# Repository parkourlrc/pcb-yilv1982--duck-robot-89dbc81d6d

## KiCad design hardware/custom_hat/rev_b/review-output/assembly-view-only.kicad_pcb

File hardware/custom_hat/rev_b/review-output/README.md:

# Rev B.0审查输出：禁止下单或制造

此处是同源审查件，成本和制造准入尚未验收，**不是可付款/可制造交付包**。`manifest.json`记录源哈希、69个拟装件、30个归并组和检查状态。

- `gerbers/`为两层RS-274X、钻孔及当前制造层，用于DFM复查。未完成最终工厂接单和封装/丝印核准，不上传旧Y6/Y7/Y8替换文件。
- `bom-grouped.csv`按精确MPN/C编号/封装/厂商归并，功能单独列；数量为每板数量，下单数量仍5片。30组中尚有精确货号/厂商规范待复核，不代表锁料。
- `cpl-all-fitted.csv`包括63个SMT和6个THT的全部69位号；THT含底面J101母座，需工厂在SMT后插装焊接。不能把同一面SMT坐标等同于经济型接单批准。
- `schematic.pdf`为主图加8个功能页；`erc.json`、`drc.json`为原生检查报告。
- 数量、备损、最低上机数、焊接工序、税费和价格必须由新B版完整报价确认。无付款授权；自由文本备注留空。

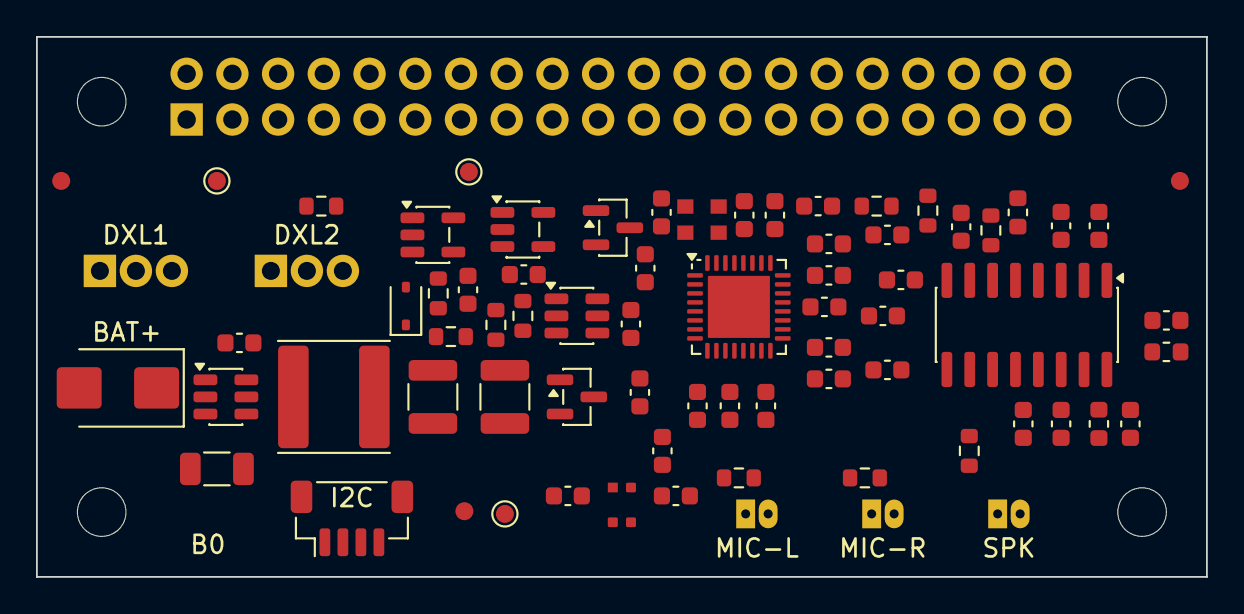
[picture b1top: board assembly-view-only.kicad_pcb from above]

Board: 2 copper layers, 65.0 x 30.0 mm, 79 parts (1 on the bottom side), 41 nets, no tracks yet.

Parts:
C301: C_1206_3216Metric
C302, C305, C401, C402, C701, C702, C703, C704, C705, C706, C707, C708, C709, C710, C711, C712, C713, C721, C722, C723, C724, C725, C731, C732, C733, C734, C735, C736, C737, C738, C739, C740: C_0603_1608Metric
C303, C304: C_1210_3225Metric
D301: D_SMB
D401: D_SOD-323
FB701, FB702, FB703: L_0603_1608Metric
FID1, FID2, FID3: Fiducial_1mm_Mask2mm_B
H1, H2: MountingHole_2.7_M2.5_Head4.5
H3, H4: MountingHole_2.7mm_M2.5
J101: Radxa40P_Zhouri_B
J401, J402: AMP2007_3P_B
J502: JST_SH_BM04B-SRSS-TB_1x04-1MP_P1.00mm_Vertical
J505, J506, J507: A1251_2P_B
L301: L_Sunlord_SWPA6045S
MK701: LMA2718_B
Q301: SOT-23
R301, R401, R402, R403, R404, R501, R502, R701, R721, R722, R731: R_0603_1608Metric
TP801, TP802, TP803: TestPoint_Pad_D1.0mm
U301, U302: TSOT-23-6
U701: TI_RHB0032E_AIC3104_EP345
U702: UMW_XC6206_SOT23_B
U801, U802: SOT-23-5
U803: SOIC-16_3.9x9.9mm_P1.27mm
Y701: YXC_2520_YSO110TR_B

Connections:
+1V8_CODEC: C703.1, C704.1, U701.32, U702.3
+3V3: C401.1, C402.1, C702.1, C705.1, C706.1, C707.1, C708.1, C709.1, C710.1, C711.1, C712.1, C713.1, C721.1, J101.1, J101.17, J502.2, MK701.4, R402.2, R403.2, R501.1, R502.1, R701.1, R731.1, TP803.1, U701.7, U701.18, U701.24, U701.25, U702.2, U801.5, U802.5, U803.5, U803.9, Y701.1, Y701.4
+5V: C734.1, C735.1, C736.1, C737.1, FB701.1, J101.2, J101.4, Q301.3, TP802.1, U302.6, U803.4, U803.13
+5V_PRE_IDEAL: C303.1, C304.1, L301.2, Q301.2, U301.1, U302.4
AMP_LEFT_INPUT: C731.2, U803.7
AMP_RIGHT_INPUT: C732.2, U803.10
AMP_R_N_RAW: FB702.1, U803.14
AMP_R_P_RAW: FB703.1, U803.16
AMP_VDD_FILT: C738.1, FB701.2, U803.6
AMP_VREF: C733.1, U803.8
AUDIO_AMP_EN: R731.2, U803.12
AUDIO_MCLK: U701.1, Y701.3
BUCK_BST: C302.1, U301.6
BUCK_SW: C302.2, L301.1, U301.5
CODEC_LEFT_LOP: C731.1, U701.27
CODEC_RIGHT_LOP: C732.1, U701.29
CODEC_RST: C701.1, J101.33, R701.2, U701.31
DXL_DATA: D401.1, J401.3, J402.3, R404.2
DXL_DATA_INT: R403.1, R404.1, U801.4, U802.2
DXL_DIR: J101.11, R401.1, U801.1, U802.1
I2C5_SCL: J101.29, J502.4, R502.2, U701.8
I2C5_SDA: J101.31, J502.3, R501.2, U701.9
I2S_BCLK: J101.12, U701.2
I2S_LRCK: J101.35, U701.3
I2S_SDI: J101.38, U701.5
I2S_SDO: J101.40, U701.4
IDEAL_GATE: Q301.1, U302.5
IDEAL_VS: C305.1, R301.2, U302.1
MICBIAS: C725.1, R721.1, R722.1, U701.15
MIC_EXT_L: C723.1, J505.2, R721.2
MIC_EXT_L_AC: C723.2, U701.10
MIC_EXT_R: C724.1, J507.2, R722.2
MIC_EXT_R_AC: C724.2, U701.12
MIC_ONBOARD_AC: C722.2, U701.16
MIC_ONBOARD_OUT: C722.1, MK701.1
POWER_GND: C301.2, C303.2, C304.2, C305.2, C401.2, C402.2, C701.2, C702.2, C703.2, C704.2, C705.2, C706.2, C707.2, C708.2, C709.2, C710.2, C711.2, C712.2, C713.2, C721.2, C725.2, C733.2, C734.2, C735.2, C736.2, C737.2, C738.2, C739.2, C740.2, D301.2, D401.2, J101.6, J101.9, J101.14, J101.20, J101.25, J101.30, J101.34, J101.39, J401.1, J402.1, J502.1, J502.MP, J505.1, J507.1, MK701.2, MK701.3, R401.2, U301.4, U302.2, U302.3, U701.6, U701.11, U701.13, U701.14, U701.17, U701.21, U701.26, U701.33, U702.1, U801.3, U802.3, U803.2, U803.11, U803.15, Y701.2
SPK_N: C739.1, FB702.2, J506.2
SPK_P: C740.1, FB703.2, J506.1
UART2_RX: J101.10, U802.4
UART2_TX: J101.8, R402.1, U801.2
VBATT_2S_IN: C301.1, D301.1, J401.2, J402.2, R301.1, TP801.1, U301.2, U301.3

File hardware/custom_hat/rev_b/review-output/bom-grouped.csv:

Designator,Quantity,MPN,LCSC Part #,Footprint,Manufacturer,Function
J101,1,2.54-2*20,C2977589,duck:Radxa40P_Zhouri_B,ZHOURI,radxa_40p
U301,1,AP63205WU-7,C2071056,Package_TO_SOT_SMD:TSOT-23-6,Diodes,power
L301,1,SWPA6045S6R8MT,C57254,Inductor_SMD:L_Sunlord_SWPA6045S,Sunlord,power
C301,1,C3216X7R1V106KT000E,C76666,Capacitor_SMD:C_1206_3216Metric,TDK,power
"C302,C305,C401,C402,C701,C704,C705,C707,C709,C711,C713,C721,C725,C735,C737",15,CC0603KRX7R9BB104,C14663,Capacitor_SMD:C_0603_1608Metric,YAGEO,audio_amp; audio_codec; audio_io; power; servo_ttl
"C303,C304",2,GRM32ER71E226KE15L,C21397,Capacitor_SMD:C_1210_3225Metric,Murata,power
U302,1,LM5050MKX-1/NOPB,C473393,Package_TO_SOT_SMD:TSOT-23-6,Texas Instruments,power
Q301,1,AO3404A,C30010,Package_TO_SOT_SMD:SOT-23,AOS,power
R301,1,0603WAF1000T5E,C22775,Resistor_SMD:R_0603_1608Metric,UNI-ROYAL,power
D301,1,SMBJ12A-E3/52,C1973121,Diode_SMD:D_SMB,Vishay,power
"J401,J402",2,CNJM A2007WV-3P,C5151076,duck:AMP2007_3P_B,CNJM,servo_ttl
U801,1,SN74LVC1G126DBVR,C7834,Package_TO_SOT_SMD:SOT-23-5,Texas Instruments,servo_ttl
U802,1,SN74LVC1G125DBVR,C23654,Package_TO_SOT_SMD:SOT-23-5,Texas Instruments,servo_ttl
"R401,R731",2,0603WAF1003T5E,C25803,Resistor_SMD:R_0603_1608Metric,UNI-ROYAL,audio_amp; servo_ttl
"R402,R403,R501,R502,R701",5,0603WAF1002T5E,C25804,Resistor_SMD:R_0603_1608Metric,UNI-ROYAL,audio_codec; i2c_expansion; servo_ttl
R404,1,0603WAF0000T5E,C21189,Resistor_SMD:R_0603_1608Metric,UNI-ROYAL,servo_ttl
D401,1,BZT52C5V1S-7-F,C151348,Diode_SMD:D_SOD-323,Diodes,servo_ttl
J502,1,BM04B-SRSS-TB(LF)(SN),C160390,Connector_JST:JST_SH_BM04B-SRSS-TB_1x04-1MP_P1.00mm_Vertical,JST,i2c_expansion
U701,1,TLV320AIC3104IRHBR,C181753,duck:TI_RHB0032E_AIC3104_EP345,Texas Instruments,audio_codec
U702,1,XC6206P182MR,C347373,duck:UMW_XC6206_SOT23_B,UMW,audio_codec
Y701,1,OT3EL89CJI-111YLC-12M,C7425459,duck:YXC_2520_YSO110TR_B,YXC,audio_codec
"C702,C706,C708,C710,C712,C722,C723,C724,C731,C732,C733,C738",12,CL10A105KB8NNNC,C15849,Capacitor_SMD:C_0603_1608Metric,SAMSUNG,audio_amp; audio_codec; audio_io
"C703,C734,C736",3,C1608X5R1A106KT000E,C76608,Capacitor_SMD:C_0603_1608Metric,TDK,audio_amp; audio_codec
MK701,1,LMA2718T421-OA5-2,C7587901,duck:LMA2718_B,LinkMems,audio_io
"J505,J507,J506",3,A1251WV-2P,C5333427,duck:A1251_2P_B,CJT,audio_amp; audio_io
"R721,R722",2,0603WAF2201T5E,C4190,Resistor_SMD:R_0603_1608Metric,UNI-ROYAL,audio_io
U803,1,PAM8406DR,C86270,Package_SO:SOIC-16_3.9x9.9mm_P1.27mm,Diodes,audio_amp
FB701,1,BLM18KG601SN1D,C85833,Inductor_SMD:L_0603_1608Metric,Murata,audio_amp
"FB702,FB703",2,PE-0603PFB121ST,C2661472,Inductor_SMD:L_0603_1608Metric,Power Ever,audio_amp
"C739,C740",2,0603CG221J500NT,C156398,Capacitor_SMD:C_0603_1608Metric,FH,audio_amp
